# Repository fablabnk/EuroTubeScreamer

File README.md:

This project is a Eurorack version of the [AionFX Stratus](https://aionfx.com/project/stratus-classic-overdrive/)

The original schematic can be found in the [PCB-Only Build Doc PDF](https://aionfx.com/app/files/docs/stratus_documentation.pdf)

The main issues in modifying the design to Eurorack format are:
- converting 12v to 9V (maybe using a LM7809)
- adding CV to the potis or using a 3.2 mini jack with an opener, so that CV would replace the poti

The ADC Inputs section of the [Daisy.patch schematics](https://daisy.nyc3.cdn.digitaloceanspaces.com/products/patch/ES_Daisy_Patch_Rev4.pdf)  might give some clue as to how to combine CV Inputs and pots.

See also: https://modwiggler.com/forum/viewtopic.php?t=87748

# Reproducing the Schematic

See `EuroTubeScreamer.kicad_sch` for the intial reproduction.

Some questions and answers:
- What do 'in' and 'out' represent? I guess the signal from the 1/4" jack tips?
	- I guess I need to replace these with 
	- In the 'wiring diagram' section we can see that there are two PCBs, a main board and a bypass board
	- Schematic for the bypass board is here: https://aionfx.com/app/files/docs/3pdt_bypass_documentation.pdf
	 
- 100R and 220R mean 100Ω and 220Ω respectively
- The diodes on the schematic don't a value, but they are 1N914's
- Why are there two LEDs in the main board schematic?
- In the bypass board schematic, we have a 3PDT footswitch, but no inbuilt schematic symbol or footprint for it
	- what will we replace this with in a eurorack context - guess just a normal 3PDT switch

https://github.com/benwis/SparkFun-Kicad-Libraries

For a couple of components there were no matching symbols i.e.
- for the 2N5088 transistor I am substituting 2N3904
- for the JRC4558D dual op amp I am substituting the RC4558
I will double check the details later to see if these subsitutions are appropriate.

## Power distribution

To create the RA and RB power sources the recommended approach is to first place a standard +9V power source (or any other named source), then edited its symbol and change both it's label (at the top) and pin name (right in the centre) to RA/RB.

To me, when deriving RA and RB from the +9V the power is an output, whereas in other parts of the circuit when I'm using it, it is an input. But for now I used the same symbols, all with Pin Properties -> Electrical type: Power input

# Next steps

1. [DONE] Assign footprints for the pots, jack inputs, switches and LEDs
2. Make a basic layout for the front panel and PCBs
	- There will likely be two PCBs, one for the front panel components and one for the
3. Complete the circuit by solving the main issues
	- Getting power from 12V down to 9V
	- Combining voltages from input pots + CV input jacks
	- Ensuring the inputs and outputs are at eurorack levels (10V)
4. Route the circuit

# Workflow

# Things I learned

- Two projects cannot be opened side by side in one instance of KiCad, instead to you have create a new instance e.g. right click on app icon and choose `New Window`
- Once the two projects are opened in this way, you can copy elements between them
- To wire the switches to the PCB using hookup wire I created a new footprint called `TwoHole_Connector` consisting simply of two pads

# Power

For now I'm:
- bringing in +12V from eurorack PSU
- connecting it to where the 9v came in, in the original circuit
- creating a 10V ref to be used to keep our CV input/pot in the right rack (10vpp)

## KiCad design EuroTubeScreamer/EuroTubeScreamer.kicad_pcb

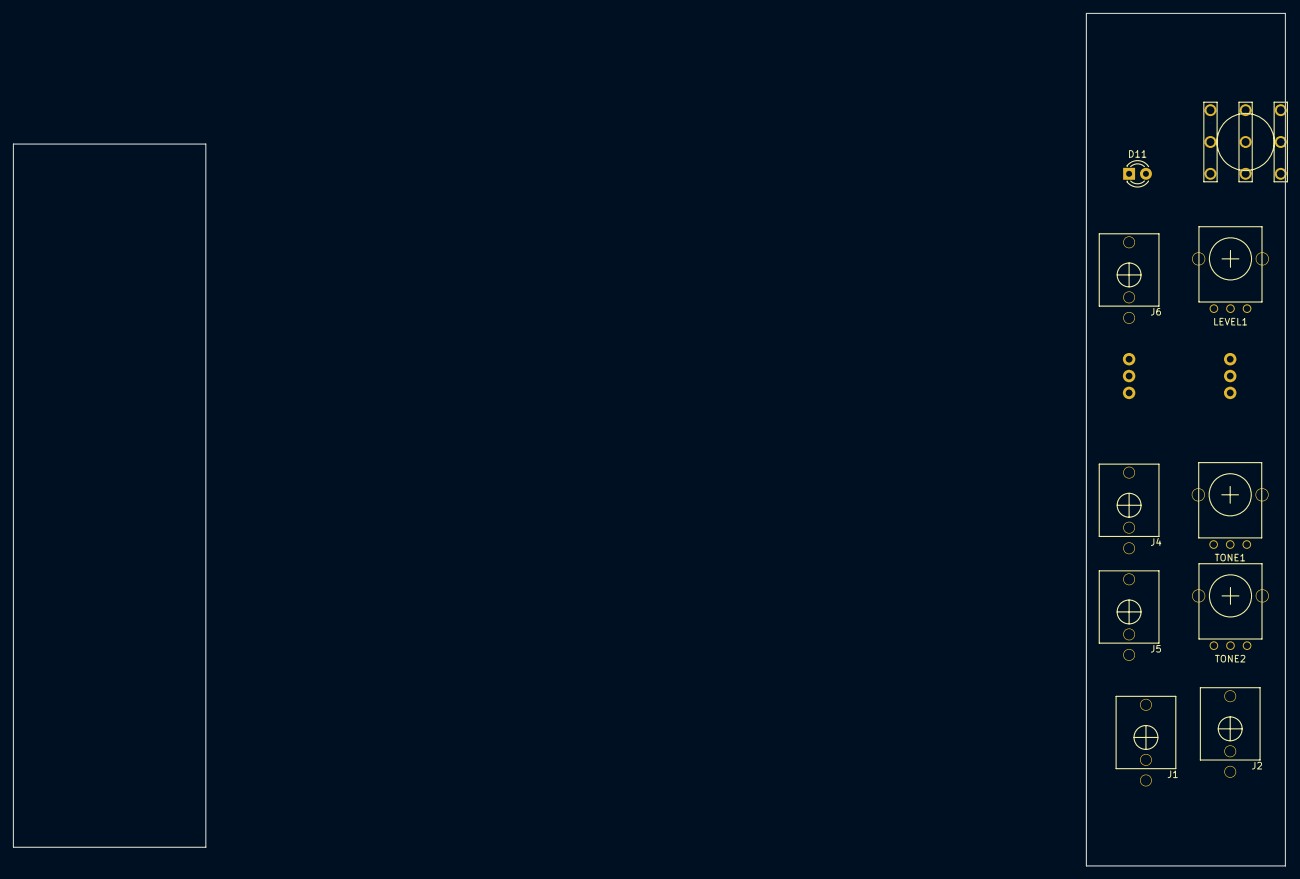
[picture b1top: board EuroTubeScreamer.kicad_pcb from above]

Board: 2 copper layers, 30.0 x 128.5 mm, 12 parts (0 on the bottom side), 4 nets, no tracks yet.

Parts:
>NAME: >VALUE; SWITCH-SPDT
>NAME#2: >VALUE; SWITCH-SPDT
D11: LED; LED_D3.0mm
FS1: BYPASS_SWITCH-3PDT; STOMP-SWITCH-3PDT
J1: AUDIO IN; PJ301M-12_T_S
J2: AUDIO OUT; PJ301M-12_T_S
J4: CV IN TONE1; PJ301M-12_T_S
J5: CV IN TONE2; PJ301M-12_T_S
J6: CV IN LEVEL1; PJ301M-12_T_S
LEVEL1: 100K; Alpha9mmPot
TONE1, TONE2: 20K; Alpha9mmPot

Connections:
GND: FS1.P$5, J1.S, J2.S, J4.S
unnamed: D11.1 (K), FS1.P$6 (S)
unnamed: FS1.P$3 (S), FS1.P$4 (O)
unnamed: TONE1.2, TONE1.3

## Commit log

2024-04-03 2nd commit
2024-04-05 Reproduced the schematic
2024-04-06 added bypass board to schematic and made a start on a panel layout
